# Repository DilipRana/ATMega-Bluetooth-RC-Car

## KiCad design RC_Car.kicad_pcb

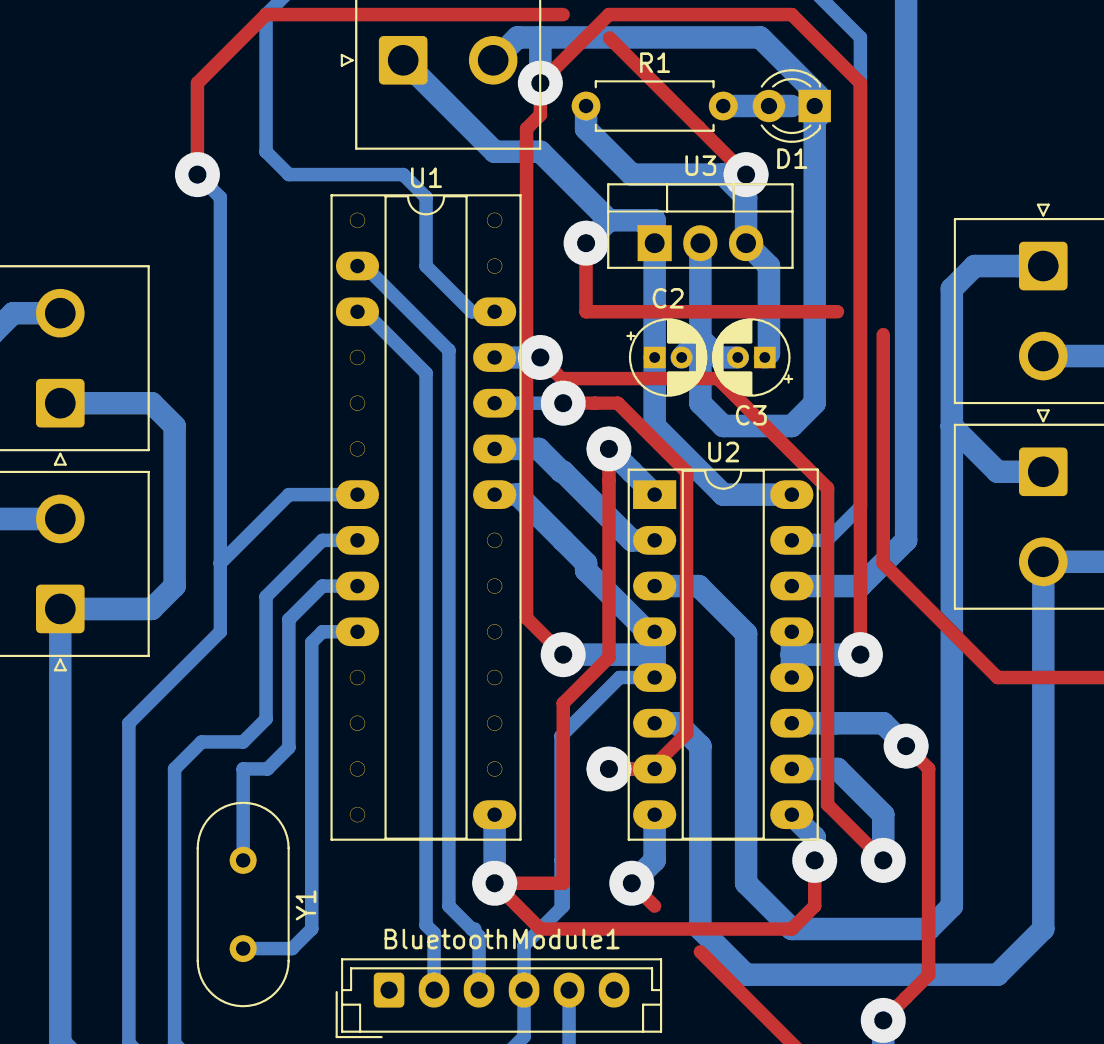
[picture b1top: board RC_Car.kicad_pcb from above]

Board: 2 copper layers, 14 parts (0 on the bottom side), 17 nets.

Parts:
BluetoothModule1: Conn_01x06; JST_EH_B06B-EH-A_1x06_P2.50mm_Vertical
C2, C3: CAP; CP_Radial_D4.0mm_P1.50mm
D1: LED; LED_D3.0mm_IRGrey
J4: 12V Supply; JST_NV_B02P-NV_1x02_P5.00mm_Vertical
Motor1, Motor2, Motor3, Motor4: Conn_01x02_Female; JST_NV_B02P-NV_1x02_P5.00mm_Vertical
R1: R; R_Axial_DIN0207_L6.3mm_D2.5mm_P7.62mm_Horizontal
U1: ATmega328P-PU; DIP-28_W7.62mm_Socket_LongPads
U2: L293D; DIP-16_W7.62mm_Socket_LongPads
U3: LM7805_TO220; TO-220-3_Vertical
Y1: Crystal; Crystal_HC18-U_Vertical

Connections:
+12V: C2.1, J4.1, U2.8, U2.16, U3.1
unnamed: BluetoothModule1.5, C3.1, R1.1, U1.7, U3.3
unnamed: U1.9, Y1.1
unnamed: U1.10, Y1.2
unnamed: D1.2, R1.2
unnamed: Motor1.1, Motor2.1, U2.3
unnamed: Motor1.2, Motor2.2, U2.6
unnamed: Motor3.1, Motor4.1, U2.11
unnamed: Motor3.2, Motor4.2, U2.14
unnamed: U1.15, U2.1, U2.9
unnamed: U1.23, U2.2
unnamed: U1.24, U2.7
unnamed: U1.25, U2.10
unnamed: U1.26, U2.15
RXD: BluetoothModule1.2, U1.3
TXD: BluetoothModule1.3, U1.2
gnd: BluetoothModule1.4, C2.2, C3.2, D1.1, J4.2, U1.8, U1.22, U2.4, U2.5, U2.12, U2.13, U3.2

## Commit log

2023-05-27 Design Completion
